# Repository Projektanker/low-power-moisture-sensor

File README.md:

# Low power moisture sensor :droplet: :tulip:

The goal is to develop a simple, energy-saving soil moisture sensor for your indoor plants. 

## Key features
  - No battery required: solar powered
  - Simple usage: LEDs shows the soil moisture

## Links
  - [about moisture sensors](https://www.ugt-online.de/produkte/bodenkunde/bodenfeuchte/ueber-bodenfeuchtesensoren/)
  - [capacitive sensor](https://www.ramser-elektro.at/shop/bausaetze-und-platinen/giesomat-kapazitiver-bodenfeuchtesensor-erdfeuchtesensor-mit-beschichtung/)
  - [SMT50 - FDR sensor](http://www.truebner.de/smt50)
  - [VH400 - TDR (?) sensor](https://www.vegetronix.com/Products/VH400/)

### TDR
  - [eevblog Building a poor man's Time Domain Reflectometer](https://www.eevblog.com/forum/projects/building-a-poor-man_s-time-domain-reflectometer/)

### Capacitive sensors
  - [capacitor design with useful links in the comment section](http://zerocharactersleft.blogspot.com/2011/11/pcb-as-capacitive-soil-moisture-sensor.html)
  - [chirp!](https://wemakethings.net/chirp/)

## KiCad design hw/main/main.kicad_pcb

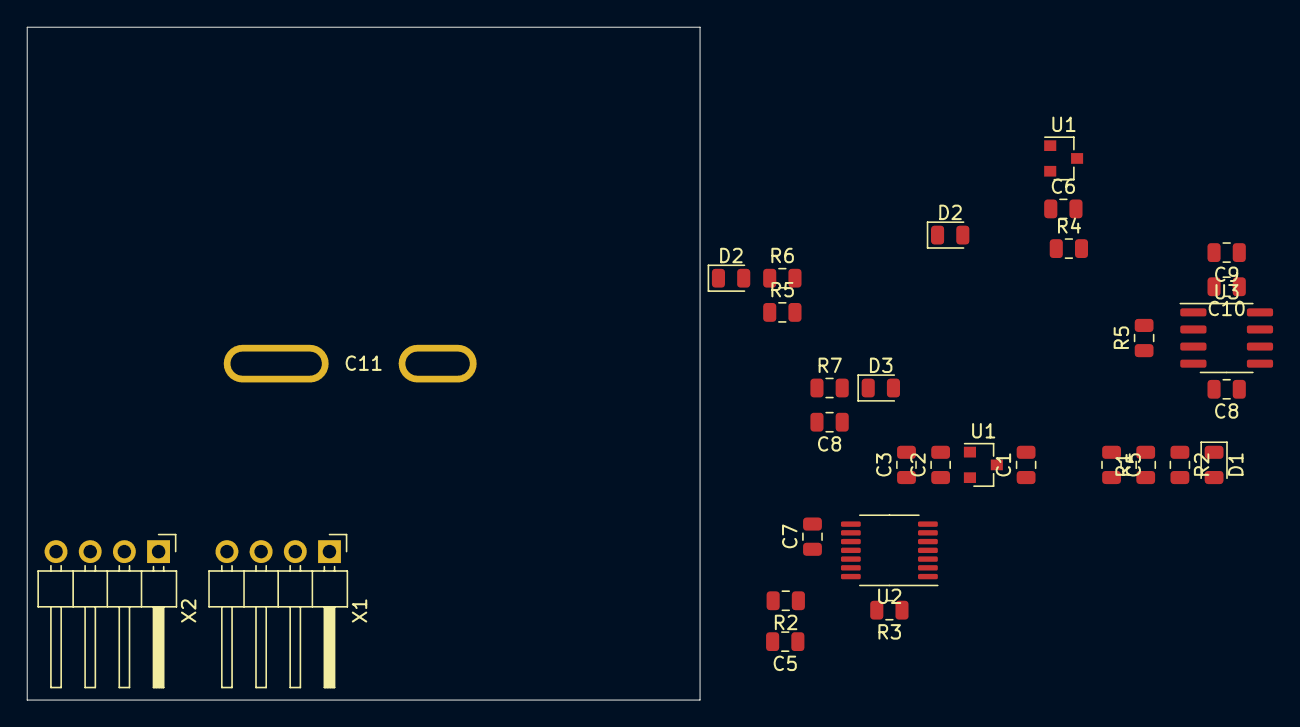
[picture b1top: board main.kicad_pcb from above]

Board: 2 copper layers, 50.0 x 50.0 mm, 31 parts (0 on the bottom side), 19 nets, no tracks yet.

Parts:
C1, C2, C6, C8#2, C9: 10u_16V; C_0805_2012Metric
C3, C5, C5#2, C7, C8, C10: 100n_50V; C_0805_2012Metric
C11: Sensor; sensor
D1, D2#2, D3: TS4148RYG; D_0805_2012Metric
D2: SS14HE; D_0805_2012Metric
R1, R2, R5#2, R6, R7: ?; R_0805_2012Metric
R2#2, R4, R5: 100K; R_0805_2012Metric
R3: 0R; R_0805_2012Metric
U1: MCP1703A-1802; SOT-23
U1#2: MCP1703A-3302; SOT-23
U2: STM32L011D3; TSSOP-14_4.4x5mm_P0.65mm
U3: LMC555xM; SOIC-8_3.9x4.9mm_P1.27mm
X1, X2: 01x04_P2.54mm_Hor; PinHeader_1x04_P2.54mm_Horizontal

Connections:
/ADC_IN7: C8#2.1, D3.1, R7.2, U2.8
/GPIO_EXTI15: C5.1, R2.1
/LPUART1_RX: R1.2, U2.5, X2.4
/LPUART1_TX: U2.6, X2.3
/Q: R5.1, U3.3
/RCC_MCO: D2#2.1, R5#2.1, U2.11
/SYS_SWCLK: U2.14, X1.4
/SYS_SWDIO: U2.13, X1.3
/Vsens: C11.1, R5.2, U3.2, U3.6
/~RST: C5#2.2, R2#2.1, U2.4
/~TRST: R4.2, U3.4
GND: C1.2, C2.2, C3.2, C5.2, C5#2.1, C6.2, C7.2, C8.2, C8#2.2, C9.2, C10.2, C11.2, R1.1, R3.2, R4.1, R7.1, U1.1, U1#2.1, U2.9, U3.1, X1.2, X2.2
unnamed: D3.2, R5#2.2, R6.2
unnamed: C8.1, U3.5
unnamed: D1.2, X2.1
unnamed: D2.2, D2#2.2, R6.1
unnamed: R3.1, U2.1
VDC: C1.1, D1.1, U1.3, U1#2.3
VDD: C2.1, C3.1, C6.1, C7.1, C9.1, C10.1, R2#2.2, U1.2, U1#2.2, U2.10, U3.8, X1.1

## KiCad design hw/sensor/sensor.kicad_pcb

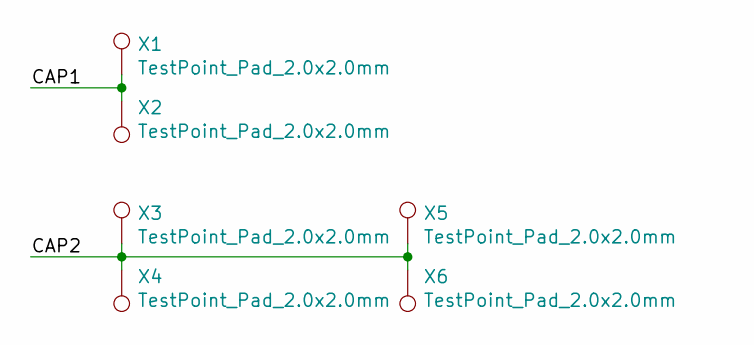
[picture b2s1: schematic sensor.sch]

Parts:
X1, X2, X3, X4, X5, X6: TestPoint_Pad_2.0x2.0mm

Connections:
/CAP1: X1.1, X2.1
/CAP2: X3.1, X4.1, X5.1, X6.1

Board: 2 copper layers, 6 parts (3 on the bottom side), 2 nets, no tracks yet.

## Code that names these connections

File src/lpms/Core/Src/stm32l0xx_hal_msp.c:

/* USER CODE BEGIN Header */
/**
  ******************************************************************************
  * File Name          : stm32l0xx_hal_msp.c
  * Description        : This file provides code for the MSP Initialization 
  *                      and de-Initialization codes.
  ******************************************************************************
  * @attention
  *
  * <h2><center>&copy; Copyright (c) 2020 STMicroelectronics.
  * All rights reserved.</center></h2>
  *
  * This software component is licensed by ST under BSD 3-Clause license,
  * the "License"; You may not use this file except in compliance with the
  * License. You may obtain a copy of the License at:
  *                        opensource.org/licenses/BSD-3-Clause
  *
  ******************************************************************************
  */
/* USER CODE END Header */

/* Includes ------------------------------------------------------------------*/
#include "main.h"
/* USER CODE BEGIN Includes */

/* USER CODE END Includes */

/* Private typedef -----------------------------------------------------------*/
/* USER CODE BEGIN TD */

/* USER CODE END TD */

/* Private define ------------------------------------------------------------*/
/* USER CODE BEGIN Define */
 
/* USER CODE END Define */

/* Private macro -------------------------------------------------------------*/
/* USER CODE BEGIN Macro */

/* USER CODE END Macro */

/* Private variables ---------------------------------------------------------*/
/* USER CODE BEGIN PV */

/* USER CODE END PV */

/* Private function prototypes -----------------------------------------------*/
/* USER CODE BEGIN PFP */

/* USER CODE END PFP */

/* External functions --------------------------------------------------------*/
/* USER CODE BEGIN ExternalFunctions */

/* USER CODE END ExternalFunctions */

/* USER CODE BEGIN 0 */

/* USER CODE END 0 */
/**
  * Initializes the Global MSP.
  */
void HAL_MspInit(void)
{
  /* USER CODE BEGIN MspInit 0 */

  /* USER CODE END MspInit 0 */
  PWR_PVDTypeDef sConfigPVD = {0};

  __HAL_RCC_SYSCFG_CLK_ENABLE();
  __HAL_RCC_PWR_CLK_ENABLE();

  /* System interrupt init*/

  /** PVD Configuration 
  */
  sConfigPVD.PVDLevel = PWR_PVDLEVEL_6;
  sConfigPVD.Mode = PWR_PVD_MODE_NORMAL;
  HAL_PWR_ConfigPVD(&sConfigPVD);
  /** Enable the PVD Output 
  */
  HAL_PWR_EnablePVD();

  /* USER CODE BEGIN MspInit 1 */

  /* USER CODE END MspInit 1 */
}

/**
* @brief ADC MSP Initialization
* This function configures the hardware resources used in this example
* @param hadc: ADC handle pointer
* @retval None
*/
void HAL_ADC_MspInit(ADC_HandleTypeDef* hadc)
{
  GPIO_InitTypeDef GPIO_InitStruct = {0};
  if(hadc->Instance==ADC1)
  {
  /* USER CODE BEGIN ADC1_MspInit 0 */

  /* USER CODE END ADC1_MspInit 0 */
    /* Peripheral clock enable */
    __HAL_RCC_ADC1_CLK_ENABLE();
  
    __HAL_RCC_GPIOA_CLK_ENABLE();
    /**ADC GPIO Configuration    
    PA7     ------> ADC_IN7 
    */
    GPIO_InitStruct.Pin = GPIO_PIN_7;
    GPIO_InitStruct.Mode = GPIO_MODE_ANALOG;
    GPIO_InitStruct.Pull = GPIO_NOPULL;
    HAL_GPIO_Init(GPIOA, &GPIO_InitStruct);

  /* USER CODE BEGIN ADC1_MspInit 1 */

  /* USER CODE END ADC1_MspInit 1 */
  }

}

/**
* @brief ADC MSP De-Initialization
* This function freeze the hardware resources used in this example
* @param hadc: ADC handle pointer
* @retval None
*/
void HAL_ADC_MspDeInit(ADC_HandleTypeDef* hadc)
{
  if(hadc->Instance==ADC1)
  {
  /* USER CODE BEGIN ADC1_MspDeInit 0 */

  /* USER CODE END ADC1_MspDeInit 0 */
    /* Peripheral clock disable */
    __HAL_RCC_ADC1_CLK_DISABLE();
  
    /**ADC GPIO Configuration    
    PA7     ------> ADC_IN7 
    */
    HAL_GPIO_DeInit(GPIOA, GPIO_PIN_7);

  /* USER CODE BEGIN ADC1_MspDeInit 1 */

  /* USER CODE END ADC1_MspDeInit 1 */
  }

}

/**
* @brief LPTIM MSP Initialization
* This function configures the hardware resources used in this example
* @param hlptim: LPTIM handle pointer
* @retval None
*/
void HAL_LPTIM_MspInit(LPTIM_HandleTypeDef* hlptim)
{
  if(hlptim->Instance==LPTIM1)
  {
  /* USER CODE BEGIN LPTIM1_MspInit 0 */

  /* USER CODE END LPTIM1_MspInit 0 */
    /* Peripheral clock enable */
    __HAL_RCC_LPTIM1_CLK_ENABLE();
  /* USER CODE BEGIN LPTIM1_MspInit 1 */

  /* USER CODE END LPTIM1_MspInit 1 */
  }

}

/**
* @brief LPTIM MSP De-Initialization
* This function freeze the hardware resources used in this example
* @param hlptim: LPTIM handle pointer
* @retval None
*/
void HAL_LPTIM_MspDeInit(LPTIM_HandleTypeDef* hlptim)
{
  if(hlptim->Instance==LPTIM1)
  {
  /* USER CODE BEGIN LPTIM1_MspDeInit 0 */

  /* USER CODE END LPTIM1_MspDeInit 0 */
    /* Peripheral clock disable */
    __HAL_RCC_LPTIM1_CLK_DISABLE();
  /* USER CODE BEGIN LPTIM1_MspDeInit 1 */

  /* USER CODE END LPTIM1_MspDeInit 1 */
  }

}

/**
* @brief UART MSP Initialization
* This function configures the hardware resources used in this example
* @param huart: UART handle pointer
* @retval None
*/
void HAL_UART_MspInit(UART_HandleTypeDef* huart)
{
  GPIO_InitTypeDef GPIO_InitStruct = {0};
  if(huart->Instance==LPUART1)
  {
  /* USER CODE BEGIN LPUART1_MspInit 0 */

  /* USER CODE END LPUART1_MspInit 0 */
    /* Peripheral clock enable */
    __HAL_RCC_LPUART1_CLK_ENABLE();
  
    __HAL_RCC_GPIOA_CLK_ENABLE();
    /**LPUART1 GPIO Configuration    
    PA0-CK_IN     ------> LPUART1_RX
    PA1     ------> LPUART1_TX 
    */
    GPIO_InitStruct.Pin = GPIO_PIN_0|GPIO_PIN_1;
    GPIO_InitStruct.Mode = GPIO_MODE_AF_PP;
    GPIO_InitStruct.Pull = GPIO_NOPULL;
    GPIO_InitStruct.Speed = GPIO_SPEED_FREQ_VERY_HIGH;
    GPIO_InitStruct.Alternate = GPIO_AF6_LPUART1;
    HAL_GPIO_Init(GPIOA, &GPIO_InitStruct);

  /* USER CODE BEGIN LPUART1_MspInit 1 */

  /* USER CODE END LPUART1_MspInit 1 */
  }

}

/**
* @brief UART MSP De-Initialization
* This function freeze the hardware resources used in this example
* @param huart: UART handle pointer
* @retval None
*/
void HAL_UART_MspDeInit(UART_HandleTypeDef* huart)
{
  if(huart->Instance==LPUART1)
  {
  /* USER CODE BEGIN LPUART1_MspDeInit 0 */

  /* USER CODE END LPUART1_MspDeInit 0 */
    /* Peripheral clock disable */
    __HAL_RCC_LPUART1_CLK_DISABLE();
  
    /**LPUART1 GPIO Configuration    
    PA0-CK_IN     ------> LPUART1_RX
    PA1     ------> LPUART1_TX 
    */
    HAL_GPIO_DeInit(GPIOA, GPIO_PIN_0|GPIO_PIN_1);

  /* USER CODE BEGIN LPUART1_MspDeInit 1 */

  /* USER CODE END LPUART1_MspDeInit 1 */
  }

}

/* USER CODE BEGIN 1 */

/* USER CODE END 1 */

/************************ (C) COPYRIGHT STMicroelectronics *****END OF FILE****/

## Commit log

2020-04-01 initial development commit
2020-04-05 Added documents
2020-04-05 Changed LDO output to 1.8V
2020-04-20 removing not used datasheets
2020-04-20 changing mcu pin assignment
2020-04-20 Added timer 555 to measure sensor capacity

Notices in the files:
hw/sensor/sensor.kicad_pcb:
©Projektanker
